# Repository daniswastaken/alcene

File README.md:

<picture>
  <source
    width="100%"
    srcset="./docs/banner.avif"
    media="(prefers-color-scheme: dark)"
  />
  <source
    width="100%"
    srcset="./docs/banner.avif"
    media="(prefers-color-scheme: light), (prefers-color-scheme: no-preference)"
  />
  
</picture>

<h1 align="center">alcene.ai</h1>

<p align="center">Custom PCB board documentation — KiCad files and board design.</p>

> [!NOTE]
> This branch documents my custom PCB board and contains its KiCad files. The main branch hosts the Alcene AI codebase; go there for project context.

## About This Branch

This branch contains all KiCad files for my custom PCB board. See the main branch (`main`) for the Alcene AI project context.

### Contents

- `kicad/` — project files, schematics, footprints, and board layouts
- `docs/` — board documentation, render notes, and build info

<!--------- Board Files Section ----------->

<h1 align="center">Board Files</h1>
<p align="center">KiCad project files for the custom PCB board.</p>

## License

MIT — see [`LICENSE`](LICENSE). Copyright (c) 2026 Handaru Daniswara.

## Star History

<a href="https://star-history.com/#daniswastaken/alcene&Date">
  <picture>
    <source media="(prefers-color-scheme: dark)" srcset="https://api.star-history.com/svg?repos=daniswastaken/alcene&type=Date&theme=dark" />
    <source media="(prefers-color-scheme: light)" srcset="https://api.star-history.com/svg?repos=daniswastaken/alcene&type=Date" />
    
  </picture>
</a>

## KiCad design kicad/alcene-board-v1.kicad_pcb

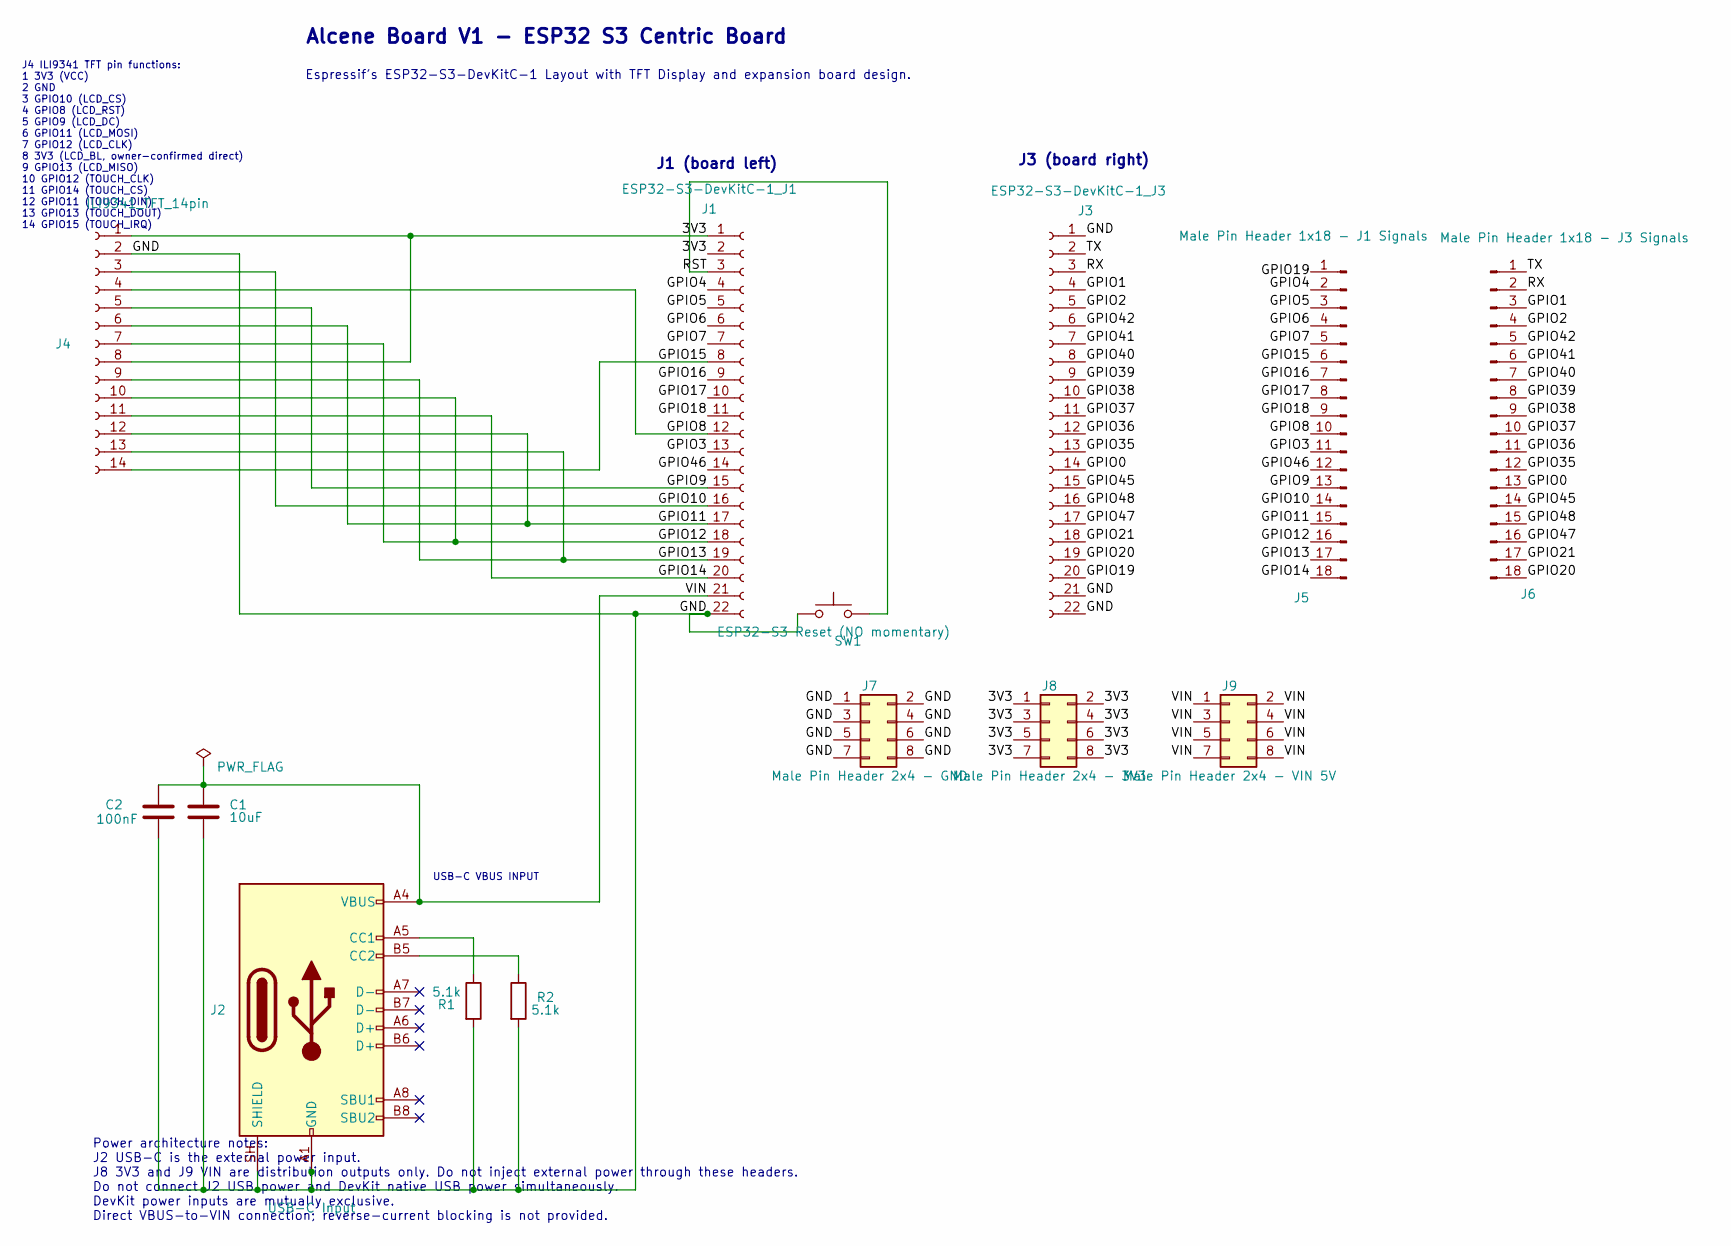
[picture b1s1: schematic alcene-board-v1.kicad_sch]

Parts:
C1: 10uF; C_0805_2012Metric; Voltage 25 V; Tolerance +/-10%; MPN GRM21BZ71E106KE15L
C2: 100nF; C_0805_2012Metric; Voltage 50 V; Tolerance +/-10%; MPN GRM21BR71H104KA01L
J1: ESP32-S3-DevKitC-1_J1; PinSocket_1x22_P2.54mm_Vertical
J2: USB-C Input; USB_C_Receptacle_GCT_USB4085
J3: ESP32-S3-DevKitC-1_J3; PinSocket_1x22_P2.54mm_Vertical
J4: ILI9341_TFT_14pin; PinSocket_1x14_P2.54mm_Vertical
J5: Male Pin Header 1x18 - J1 Signals; PinHeader_1x18_P2.54mm_Vertical
J6: Male Pin Header 1x18 - J3 Signals; PinHeader_1x18_P2.54mm_Vertical
J7: Male Pin Header 2x4 - GND; PinHeader_2x04_P2.54mm_Vertical
J8: Male Pin Header 2x4 - 3V3; PinHeader_2x04_P2.54mm_Vertical
J9: Male Pin Header 2x4 - VIN 5V; PinHeader_2x04_P2.54mm_Vertical
R1, R2: 5.1k; R_0805_2012Metric
SW1: ESP32-S3 Reset (NO momentary); SW_Push_SPST_NO_Alps_SKRK

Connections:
3V3: J1.1, J1.2, J4.1, J4.8, J8.1, J8.2, J8.3, J8.4, J8.5, J8.6, J8.7, J8.8
GND: C1.2, C2.2, J1.22, J2.A1 (GND), J2.A12 (GND), J2.B1 (GND), J2.B12 (GND), J2.SH (SHIELD), J3.1, J3.21, J3.22, J4.2, J7.1, J7.2, J7.3, J7.4, J7.5, J7.6, J7.7, J7.8, R1.2, R2.2, SW1.1
GPIO0: J3.14, J6.13
GPIO1: J3.4, J6.3
GPIO2: J3.5, J6.4
GPIO3: J1.13, J5.11
GPIO4: J1.4, J5.2
GPIO5: J1.5, J5.3
GPIO6: J1.6, J5.4
GPIO7: J1.7, J5.5
GPIO8: J1.12, J4.4, J5.10
GPIO9: J1.15, J4.5, J5.13
GPIO10: J1.16, J4.3, J5.14
GPIO11: J1.17, J4.6, J4.12, J5.15
GPIO12: J1.18, J4.7, J4.10, J5.16
GPIO13: J1.19, J4.9, J4.13, J5.17
GPIO14: J1.20, J4.11, J5.18
GPIO15: J1.8, J4.14, J5.6
GPIO16: J1.9, J5.7
GPIO17: J1.10, J5.8
GPIO18: J1.11, J5.9
GPIO19: J3.20, J5.1
GPIO20: J3.19, J6.18
GPIO21: J3.18, J6.17
GPIO35: J3.13, J6.12
GPIO36: J3.12, J6.11
GPIO37: J3.11, J6.10
GPIO38: J3.10, J6.9
GPIO39: J3.9, J6.8
GPIO40: J3.8, J6.7
GPIO41: J3.7, J6.6
GPIO42: J3.6, J6.5
GPIO45: J3.15, J6.14
GPIO46: J1.14, J5.12
GPIO47: J3.17, J6.16
GPIO48: J3.16, J6.15
unnamed: J2.A5 (CC1), R1.1
unnamed: J2.B5 (CC2), R2.1
RST: J1.3, SW1.2
RX: J3.3, J6.2
TX: J3.2, J6.1
VIN: C1.1, C2.1, J1.21, J2.A4 (VBUS), J2.A9 (VBUS), J2.B4 (VBUS), J2.B9 (VBUS), J9.1, J9.2, J9.3, J9.4, J9.5, J9.6, J9.7, J9.8

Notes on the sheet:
J3 (board right)
Alcene Board V1 - ESP32 S3 Centric Board
Espressif's ESP32-S3-DevKitC-1 Layout with TFT Display and expansion board design.
J1 (board left)
J4 ILI9341 TFT pin functions: 1 3V3 (VCC) 2 GND 3 GPIO10 (LCD_CS) 4 GPIO8 (LCD_RST) 5 GPIO9 (LCD_DC) 6 GPIO11 (LCD_MOSI) 7 GPIO12 (LCD_CLK) 8 3V3 (LCD_BL, owner-confirmed direct) 9 GPIO13 (LCD_MISO) 10 GPIO12 (TOUCH_CLK) 11 GPIO14 (TOUCH_CS) 12 GPIO11 (TOUCH_DIN) 13 GPIO13 (TOUCH_DOUT) 14 GPIO15 (T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
Power architecture notes: J2 USB-C is the external power input. J8 3V3 and J9 VIN are distribution outputs only. Do not inject external power through these headers. Do not connect J2 USB power and DevKit native USB power simultaneously. DevKit power inputs are mutually exclusive. Direct VBUS-to-VIN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
USB-C VBUS INPUT

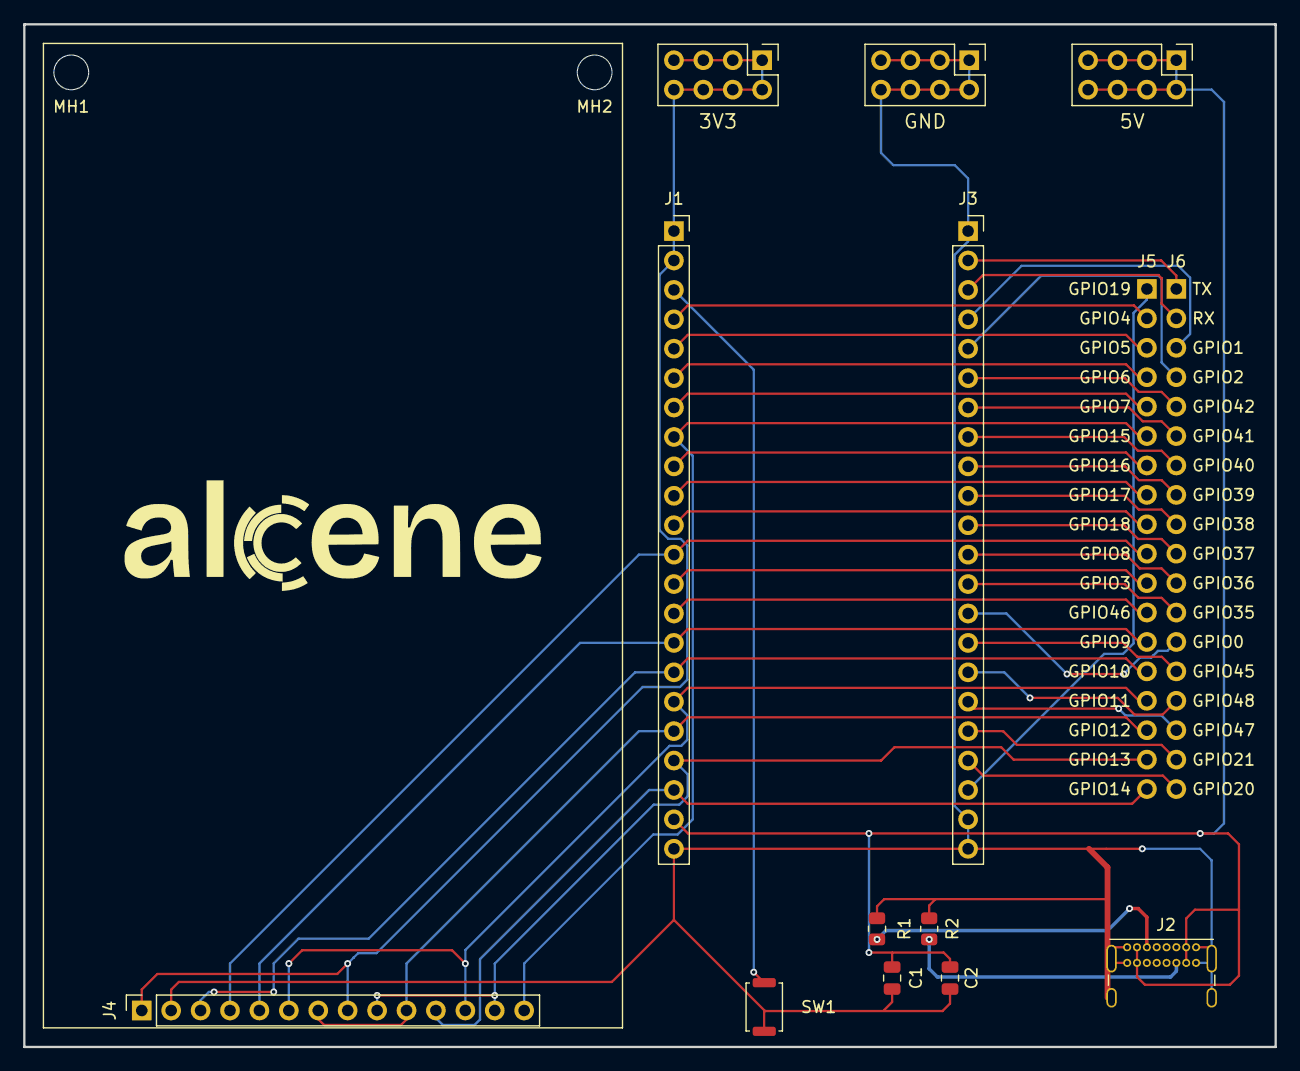
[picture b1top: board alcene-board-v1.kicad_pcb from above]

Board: 2 copper layers, 108.0 x 88.3 mm, 16 parts (0 on the bottom side), 42 nets.

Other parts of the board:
MH1, MH2: MountingHole_3mm

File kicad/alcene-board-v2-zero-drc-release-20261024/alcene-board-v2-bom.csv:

Ref,Qty,Value,Footprint
C1,1,10uF,Capacitor_SMD:C_0805_2012Metric
C2,1,100nF,Capacitor_SMD:C_0805_2012Metric
J1,1,ESP32-S3-DevKitC-1_J1,Connector_PinSocket_2.54mm:PinSocket_1x22_P2.54mm_Vertical
J2,1,USB-C Input,Connector_USB:USB_C_Receptacle_GCT_USB4085
J3,1,ESP32-S3-DevKitC-1_J3,Connector_PinSocket_2.54mm:PinSocket_1x22_P2.54mm_Vertical
J4,1,ILI9341_TFT_14pin,Connector_PinSocket_2.54mm:PinSocket_1x14_P2.54mm_Vertical
J5,1,Male Pin Header 1x18 - J1 Signals,Connector_PinHeader_2.54mm:PinHeader_1x18_P2.54mm_Vertical
J6,1,Male Pin Header 1x18 - J3 Signals,Connector_PinHeader_2.54mm:PinHeader_1x18_P2.54mm_Vertical
J7,1,Male Pin Header 2x4 - GND,Connector_PinHeader_2.54mm:PinHeader_2x04_P2.54mm_Vertical
J8,1,Male Pin Header 2x4 - 3V3,Connector_PinHeader_2.54mm:PinHeader_2x04_P2.54mm_Vertical
J9,1,Male Pin Header 2x4 - VIN 5V,Connector_PinHeader_2.54mm:PinHeader_2x04_P2.54mm_Vertical
R1,1,5.1k,Resistor_SMD:R_0805_2012Metric
R2,1,5.1k,Resistor_SMD:R_0805_2012Metric
SW1,1,ESP32-S3 Reset (NO momentary),Button_Switch_SMD:SW_Push_SPST_NO_Alps_SKRK

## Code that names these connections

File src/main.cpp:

//  alcene.ai -- ESP32-S3 boot splash
//
//  Brings up an I2C SSD1306 128x64 OLED and holds the alcene wordmark on it.
//  The panel keeps the last frame without refresh, so after setup() the splash
//  simply stays. Diagnostics go to Serial, never to the panel.
//
//  Wiring (see platformio.ini for the full pin map):
//      OLED SDA -> GPIO8      OLED SCL -> GPIO9
//
//  Everything on the S3 DevKitC-1 is 3.3 V only.

#include <Adafruit_GFX.h>
#include <Adafruit_SSD1306.h>
#include <Adafruit_NeoPixel.h>
#include <Wire.h>

#include "alcene_wordmark.h"

namespace {

// The panel matches the wordmark framebuffer exactly; taking the dimensions
// from the generated header keeps a resolution change to a single source of
// truth. ALCENE_WORDMARK_W is 128, which is byte-aligned, so the generated
// bitmap needs no per-row padding.
constexpr int kWidth = ALCENE_WORDMARK_W;
constexpr int kHeight = ALCENE_WORDMARK_H;

// Stock S3 DevKitC-1 I2C pins. The 7-pin module also wants RES on GPIO10 and
// DC on GPIO11; the 4-pin module ties those and only needs SDA/SCL.
constexpr int kSdaPin = 8;
constexpr int kSclPin = 9;

constexpr uint8_t kOledAddress = 0x3C;
constexpr int kRgbPin = 48;
constexpr uint8_t kRgbCount = 1;

Adafruit_NeoPixel rgb(kRgbCount, kRgbPin, NEO_GRB + NEO_KHZ800);

// Reset pin is -1: the 4-pin module has no RES line, and the 7-pin one is
// clocked by the SSD1306's own charge-pump sequence well enough to come up.
Adafruit_SSD1306 display(kWidth, kHeight, &Wire, -1);

// The generated bitmap is already 128x64 with the wordmark centred inside it,
// so this is a straight full-panel blit. If the header ever carries art that is
// smaller than the panel, drawBitmap still anchors at the top-left, which is why
// centring is baked in at generation time rather than here.
void drawWordmark() {
  display.clearDisplay();
  display.drawBitmap(0, 0, ALCENE_WORDMARK, kWidth, kHeight, SSD1306_WHITE);
  display.display();
}

const char *revision() {
  switch (ESP.getChipRevision()) {
    case 0: return "0.0";
    case 1: return "0.1";
    case 2: return "0.2";
    default: return "?";
  }
}

void reportToSerial() {
  Serial.println();
  Serial.println(F("alcene.ai -- ESP32-S3"));
  Serial.print(F("  chip    : "));
  Serial.println(ESP.getChipModel());
  Serial.print(F("  rev     : "));
  Serial.println(revision());
  Serial.print(F("  cpu     : "));
  Serial.print(ESP.getCpuFreqMHz());
  Serial.println(F(" MHz"));
  Serial.print(F("  psram   : "));
  if (psramFound()) {
    Serial.print(ESP.getPsramSize() / (1024UL * 1024UL));
    Serial.println(F(" MB"));
  } else {
    Serial.println(F("not found -- check qio_opi in platformio.ini"));
  }
  Serial.print(F("  flash   : "));
  Serial.print(ESP.getFlashChipSize() / (1024UL * 1024UL));
  Serial.println(F(" MB"));
  Serial.print(F("  heap    : "));
  Serial.print(ESP.getFreeHeap() / 1024UL);
  Serial.println(F(" KB"));
  Serial.print(F("  oled    : "));
  Serial.println(display.width() * display.height() ? "ok" : "failed");
}

void halt(const __FlashStringHelper *why) {
  Serial.println(why);
  display.clearDisplay();
  display.setTextColor(SSD1306_WHITE);
  display.setTextSize(1);
  display.setCursor(0, 0);
  display.println(F("alcene.ai"));
  display.println();
  display.println(F("OLED not found"));
  display.println(F("check SDA=GPIO8"));
  display.println(F("SCL=GPIO9, addr 0x3C"));
  display.display();
  for (;;) {
    delay(1000);
  }
}

}  // namespace

void setup() {
  Serial.begin(115200);
  const uint32_t start = millis();
  while (!Serial && millis() - start < 2000) {
    delay(10);
  }

  rgb.begin();
  rgb.setBrightness(10);  // low, not blinding
  rgb.clear();
  rgb.show();

  Wire.begin(kSdaPin, kSclPin);
  Wire.setClock(400000);

  if (!display.begin(SSD1306_SWITCHCAPVCC, kOledAddress)) {
    halt(F("SSD1306 not responding at 0x3C."));
  }

  display.clearDisplay();
  display.display();
  delay(50);

  drawWordmark();
  reportToSerial();
}

void loop() {
  static int phase = 0;  // 0..599 full R→G→B→R
uint8_t r, g, b;
int p = phase % 600;
if (p < 200) {            // red → green
  r = 255 - p * 255 / 200;
  g = p * 255 / 200;
  b = 0;
} else if (p < 400) {     // green → blue
  p -= 200;
  r = 0;
  g = 255 - p * 255 / 200;
  b = p * 255 / 200;
} else {                  // blue → red
  p -= 400;
  r = p * 255 / 200;
  g = 0;
  b = 255 - p * 255 / 200;
}
rgb.setPixelColor(0, rgb.Color(r, g, b));
rgb.show();
phase += 6;             // 600/6 = 100 steps × 40ms = 4 s ring
if (phase >= 600) phase = 0;
delay(30);
}

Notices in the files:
README.md:
<img alt="License" src="https://img.shields.io/badge/License-MIT-22c55e?style=flat&logo=data:image/svg%2Bxml;base64,PHN2ZyB4bWxucz0iaHR0cDovL3d3dy53My5vcmcvMjAwMC9zdmciIHdpZHRoPSIyNCIgaGVpZ2h0PSIyNCIgdmlld0JveD0iMCAwIDI0IDI0IiBmaWxsPSJub25lIiBzdHJva2U9IiNmZmZmZmYiIHN0cm9rZS13aWR0aD0iMiIgc3Ryb2tlLWxp
